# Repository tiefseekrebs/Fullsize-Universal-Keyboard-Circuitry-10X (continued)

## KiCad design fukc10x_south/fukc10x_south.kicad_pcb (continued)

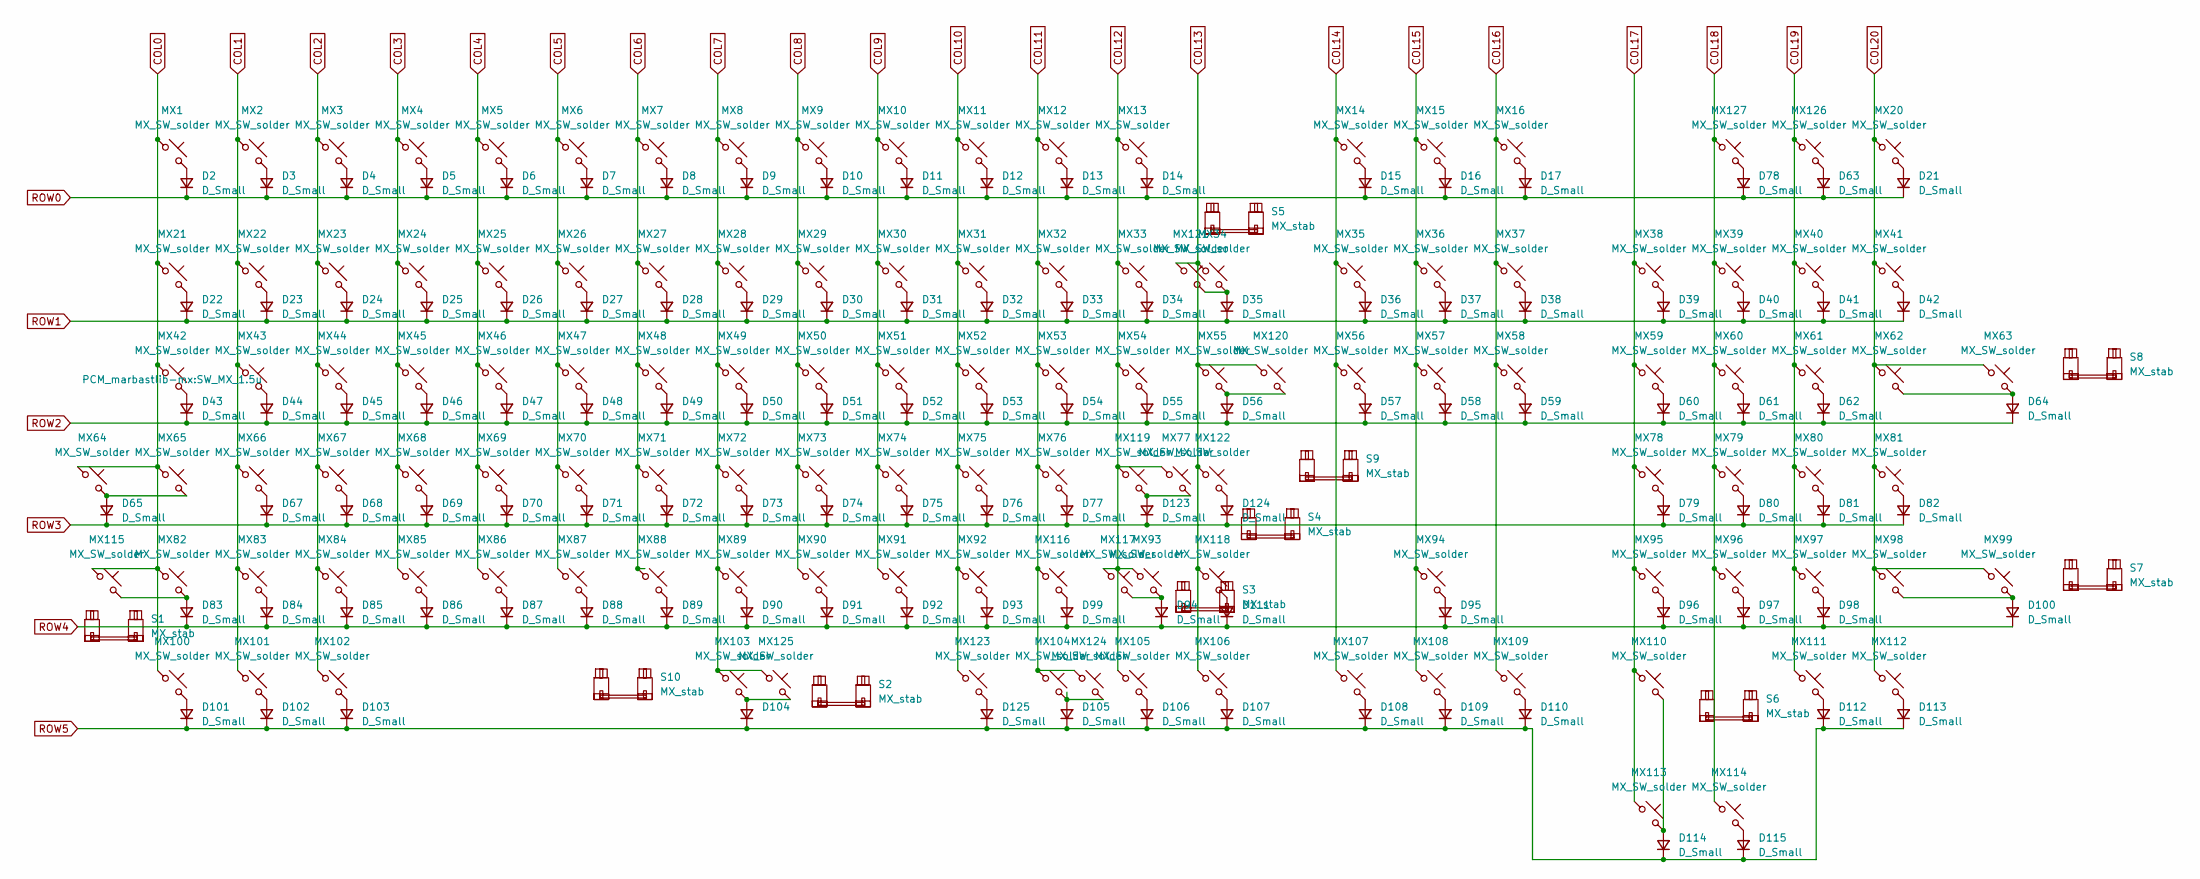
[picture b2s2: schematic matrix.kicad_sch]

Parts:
D2, D3, D4, D5, D6, D7, D8, D9, D10, D11, D12, D13, D14, D15, D16, D17, D21, D22, D23, D24, D25, D26, D27, D28, D29, D30, D31, D32, D33, D34, D35, D36, D37, D38, D39, D40, D41, D42, D43, D44, D45, D46, D47, D48, D49, D50, D51, D52, D53, D54, D55, D56, D57, D58, D59, D60, D61, D62, D63, D64, D65, D67, D68, D69, D70, D71, D72, D73, D74, D75, D76, D77, D78, D79, D80, D81, D82, D83, D84, D85, D86, D87, D88, D89, D90, D91, D92, D93, D94, D95, D96, D97, D98, D99, D100, D101, D102, D103, D104, D105, D106, D107, D108, D109, D110, D111, D112, D113, D114, D115, D123, D124, D125: D_Small; D_SOD-123; LCSC C81598
MX1, MX2, MX3, MX4, MX5, MX6, MX7, MX8, MX9, MX10, MX11, MX12, MX13, MX14, MX15, MX16, MX20, MX21, MX22, MX23, MX24, MX25, MX26, MX27, MX28, MX29, MX30, MX31, MX32, MX33, MX34, MX35, MX36, MX37, MX38, MX39, MX40, MX41, MX43, MX44, MX45, MX46, MX47, MX48, MX49, MX50, MX51, MX52, MX53, MX54, MX56, MX57, MX58, MX59, MX60, MX61, MX62, MX63, MX66, MX67, MX68, MX69, MX70, MX71, MX72, MX73, MX74, MX75, MX76, MX77, MX78, MX79, MX80, MX81, MX82, MX83, MX84, MX85, MX86, MX87, MX88, MX89, MX90, MX91, MX92, MX93, MX94, MX95, MX96, MX97, MX98, MX99, MX101, MX103, MX105, MX107, MX108, MX109, MX110, MX111, MX112, MX113, MX114, MX116, MX118, MX119, MX120, MX121, MX122, MX124, MX125, MX126, MX127: MX_SW_solder; SW_MX_1u
MX42, MX55, MX100, MX102, MX104, MX106, MX123: MX_SW_solder; SW_MX_1.5u
MX64, MX117: MX_SW_solder; SW_MX_1.75u
MX65: MX_SW_solder; SW_MX_1.75u_STP_1.25
MX115: MX_SW_solder; SW_MX_1.25u
S1, S4: MX_stab; STAB_MX_2.25u
S2: MX_stab; STAB_MX_7u
S3: MX_stab; STAB_MX_2.75u
S5, S6, S7, S8: MX_stab; STAB_MX_2u
S9: MX_stab; STAB_MX_ISO-ROT
S10: MX_stab; STAB_MX_6u

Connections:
COL0: MX1.1, MX21.1, MX42.1, MX64.1, MX65.1, MX82.1, MX100.1, MX115.1; also elsewhere on the board
COL1: MX2.1, MX22.1, MX43.1, MX66.1, MX83.1, MX101.1; also elsewhere on the board
COL2: MX3.1, MX23.1, MX44.1, MX67.1, MX84.1, MX102.1; also elsewhere on the board
COL3: MX4.1, MX24.1, MX45.1, MX68.1, MX85.1; also elsewhere on the board
COL4: MX5.1, MX25.1, MX46.1, MX69.1, MX86.1; also elsewhere on the board
COL5: MX6.1, MX26.1, MX47.1, MX70.1, MX87.1; also elsewhere on the board
COL6: MX7.1, MX27.1, MX48.1, MX71.1, MX88.1; also elsewhere on the board
COL7: MX8.1, MX28.1, MX49.1, MX72.1, MX89.1, MX103.1, MX125.1; also elsewhere on the board
COL8: MX9.1, MX29.1, MX50.1, MX73.1, MX90.1; also elsewhere on the board
COL9: MX10.1, MX30.1, MX51.1, MX74.1, MX91.1; also elsewhere on the board
COL10: MX11.1, MX31.1, MX52.1, MX75.1, MX92.1, MX123.1; also elsewhere on the board
COL11: MX12.1, MX32.1, MX53.1, MX76.1, MX104.1, MX116.1, MX124.1; also elsewhere on the board
COL12: MX13.1, MX33.1, MX54.1, MX77.1, MX93.1, MX105.1, MX117.1, MX119.1; also elsewhere on the board
COL13: MX34.1, MX55.1, MX106.1, MX118.1, MX120.1, MX121.1, MX122.1; also elsewhere on the board
COL14: MX14.1, MX35.1, MX56.1, MX107.1; also elsewhere on the board
COL15: MX15.1, MX36.1, MX57.1, MX94.1, MX108.1; also elsewhere on the board
COL16: MX16.1, MX37.1, MX58.1, MX109.1; also elsewhere on the board
COL17: MX38.1, MX59.1, MX78.1, MX95.1, MX110.1, MX113.1; also elsewhere on the board
COL18: MX39.1, MX60.1, MX79.1, MX96.1, MX114.1, MX127.1; also elsewhere on the board
COL19: MX40.1, MX61.1, MX80.1, MX97.1, MX111.1, MX126.1; also elsewhere on the board
COL20: MX20.1, MX41.1, MX62.1, MX63.1, MX81.1, MX98.1, MX99.1, MX112.1; also elsewhere on the board
unnamed: D2.2 (A), MX1.2
unnamed: D3.2 (A), MX2.2
unnamed: D4.2 (A), MX3.2
unnamed: D5.2 (A), MX4.2
unnamed: D6.2 (A), MX5.2
unnamed: D7.2 (A), MX6.2
unnamed: D8.2 (A), MX7.2
unnamed: D9.2 (A), MX8.2
unnamed: D10.2 (A), MX9.2
unnamed: D11.2 (A), MX10.2
unnamed: D12.2 (A), MX11.2
unnamed: D13.2 (A), MX12.2
unnamed: D14.2 (A), MX13.2
unnamed: D15.2 (A), MX14.2
unnamed: D16.2 (A), MX15.2
unnamed: D17.2 (A), MX16.2
unnamed: D21.2 (A), MX20.2
unnamed: D22.2 (A), MX21.2
unnamed: D23.2 (A), MX22.2
unnamed: D24.2 (A), MX23.2
unnamed: D25.2 (A), MX24.2
unnamed: D26.2 (A), MX25.2
unnamed: D27.2 (A), MX26.2
unnamed: D28.2 (A), MX27.2
unnamed: D29.2 (A), MX28.2
unnamed: D30.2 (A), MX29.2
unnamed: D31.2 (A), MX30.2
unnamed: D32.2 (A), MX31.2
unnamed: D33.2 (A), MX32.2
unnamed: D34.2 (A), MX33.2
unnamed: D35.2 (A), MX34.2, MX121.2
unnamed: D36.2 (A), MX35.2
unnamed: D37.2 (A), MX36.2
unnamed: D38.2 (A), MX37.2
unnamed: D39.2 (A), MX38.2
unnamed: D40.2 (A), MX39.2
unnamed: D41.2 (A), MX40.2
unnamed: D42.2 (A), MX41.2
unnamed: D43.2 (A), MX42.2
unnamed: D44.2 (A), MX43.2
unnamed: D45.2 (A), MX44.2
unnamed: D46.2 (A), MX45.2
unnamed: D47.2 (A), MX46.2
unnamed: D48.2 (A), MX47.2
unnamed: D49.2 (A), MX48.2
unnamed: D50.2 (A), MX49.2
unnamed: D51.2 (A), MX50.2
unnamed: D52.2 (A), MX51.2
unnamed: D53.2 (A), MX52.2
unnamed: D54.2 (A), MX53.2
unnamed: D55.2 (A), MX54.2
unnamed: D56.2 (A), MX55.2, MX120.2
unnamed: D57.2 (A), MX56.2
unnamed: D58.2 (A), MX57.2
unnamed: D59.2 (A), MX58.2
unnamed: D60.2 (A), MX59.2
unnamed: D61.2 (A), MX60.2
unnamed: D62.2 (A), MX61.2
unnamed: D63.2 (A), MX126.2
unnamed: D64.2 (A), MX62.2, MX63.2
unnamed: D65.2 (A), MX64.2, MX65.2
unnamed: D67.2 (A), MX66.2
unnamed: D68.2 (A), MX67.2
unnamed: D69.2 (A), MX68.2
unnamed: D70.2 (A), MX69.2
unnamed: D71.2 (A), MX70.2
unnamed: D72.2 (A), MX71.2
unnamed: D73.2 (A), MX72.2
unnamed: D74.2 (A), MX73.2
unnamed: D75.2 (A), MX74.2
unnamed: D76.2 (A), MX75.2
unnamed: D77.2 (A), MX76.2
unnamed: D78.2 (A), MX127.2
unnamed: D79.2 (A), MX78.2
unnamed: D80.2 (A), MX79.2
unnamed: D81.2 (A), MX80.2
unnamed: D82.2 (A), MX81.2
unnamed: D83.2 (A), MX82.2, MX115.2
unnamed: D84.2 (A), MX83.2
unnamed: D85.2 (A), MX84.2
unnamed: D86.2 (A), MX85.2
unnamed: D87.2 (A), MX86.2
unnamed: D88.2 (A), MX87.2
unnamed: D89.2 (A), MX88.2
unnamed: D90.2 (A), MX89.2
unnamed: D91.2 (A), MX90.2
unnamed: D92.2 (A), MX91.2
unnamed: D93.2 (A), MX92.2
unnamed: D94.2 (A), MX93.2, MX117.2
unnamed: D95.2 (A), MX94.2
unnamed: D96.2 (A), MX95.2
unnamed: D97.2 (A), MX96.2
unnamed: D98.2 (A), MX97.2
unnamed: D99.2 (A), MX116.2
unnamed: D100.2 (A), MX98.2, MX99.2
unnamed: D101.2 (A), MX100.2
unnamed: D102.2 (A), MX101.2
unnamed: D103.2 (A), MX102.2
unnamed: D104.2 (A), MX103.2, MX125.2
unnamed: D105.2 (A), MX104.2, MX124.2
unnamed: D106.2 (A), MX105.2
unnamed: D107.2 (A), MX106.2
unnamed: D108.2 (A), MX107.2
unnamed: D109.2 (A), MX108.2
unnamed: D110.2 (A), MX109.2
unnamed: D111.2 (A), MX118.2
unnamed: D112.2 (A), MX111.2
unnamed: D113.2 (A), MX112.2
unnamed: D114.2 (A), MX110.2, MX113.2
unnamed: D115.2 (A), MX114.2
unnamed: D123.2 (A), MX77.2, MX119.2
unnamed: D124.2 (A), MX122.2
unnamed: D125.2 (A), MX123.2
ROW0: D2.1 (K), D3.1 (K), D4.1 (K), D5.1 (K), D6.1 (K), D7.1 (K), D8.1 (K), D9.1 (K), D10.1 (K), D11.1 (K), D12.1 (K), D13.1 (K), D14.1 (K), D15.1 (K), D16.1 (K), D17.1 (K), D21.1 (K), D63.1 (K), D78.1 (K); also elsewhere on the board
ROW1: D22.1 (K), D23.1 (K), D24.1 (K), D25.1 (K), D26.1 (K), D27.1 (K), D28.1 (K), D29.1 (K), D30.1 (K), D31.1 (K), D32.1 (K), D33.1 (K), D34.1 (K), D35.1 (K), D36.1 (K), D37.1 (K), D38.1 (K), D39.1 (K), D40.1 (K), D41.1 (K), D42.1 (K); also elsewhere on the board
ROW2: D43.1 (K), D44.1 (K), D45.1 (K), D46.1 (K), D47.1 (K), D48.1 (K), D49.1 (K), D50.1 (K), D51.1 (K), D52.1 (K), D53.1 (K), D54.1 (K), D55.1 (K), D56.1 (K), D57.1 (K), D58.1 (K), D59.1 (K), D60.1 (K), D61.1 (K), D62.1 (K), D64.1 (K); also elsewhere on the board
ROW3: D65.1 (K), D67.1 (K), D68.1 (K), D69.1 (K), D70.1 (K), D71.1 (K), D72.1 (K), D73.1 (K), D74.1 (K), D75.1 (K), D76.1 (K), D77.1 (K), D79.1 (K), D80.1 (K), D81.1 (K), D82.1 (K), D123.1 (K), D124.1 (K); also elsewhere on the board
ROW4: D83.1 (K), D84.1 (K), D85.1 (K), D86.1 (K), D87.1 (K), D88.1 (K), D89.1 (K), D90.1 (K), D91.1 (K), D92.1 (K), D93.1 (K), D94.1 (K), D95.1 (K), D96.1 (K), D97.1 (K), D98.1 (K), D99.1 (K), D100.1 (K), D111.1 (K); also elsewhere on the board
ROW5: D101.1 (K), D102.1 (K), D103.1 (K), D104.1 (K), D105.1 (K), D106.1 (K), D107.1 (K), D108.1 (K), D109.1 (K), D110.1 (K), D112.1 (K), D113.1 (K), D114.1 (K), D115.1 (K), D125.1 (K); also elsewhere on the board

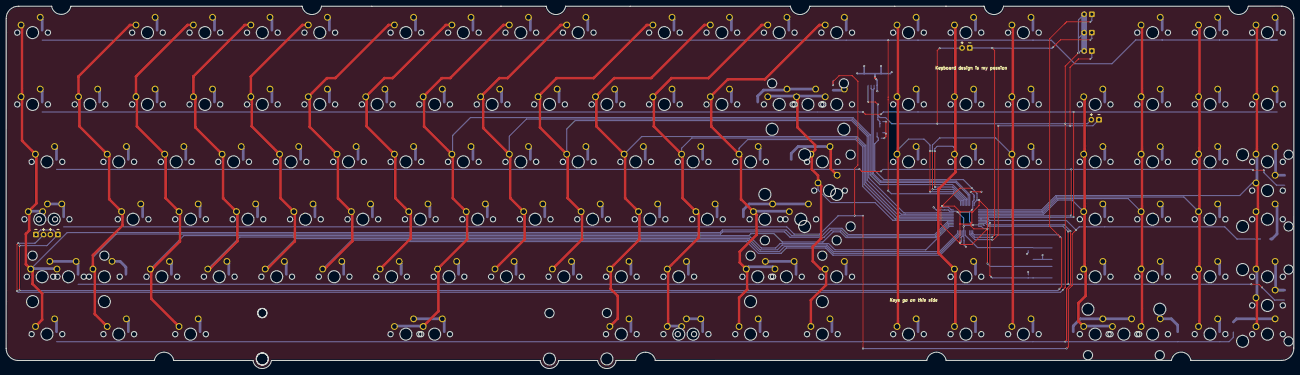
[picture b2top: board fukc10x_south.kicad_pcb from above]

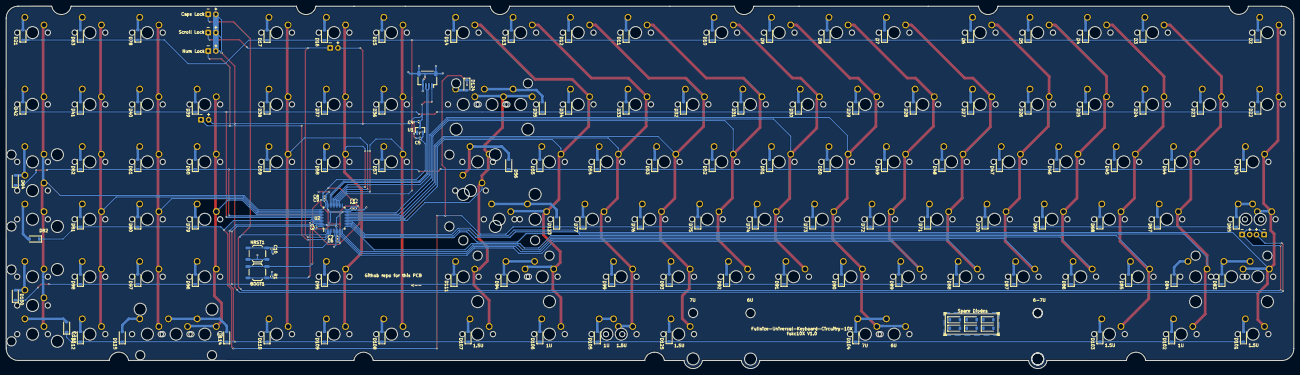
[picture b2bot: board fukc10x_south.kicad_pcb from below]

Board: 2 copper layers, 427.1 x 120.2 mm, 276 parts (135 on the bottom side), 150 nets.

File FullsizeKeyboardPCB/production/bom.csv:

Designator,Footprint,Quantity,Value,LCSC Part #
BOOT1,SW_SPST_TL3342,1,SW_BOOT0,
"C1, C8",0402,2,4.7uF,C23733
C10,0402,1,100nF,
"C2, C3, C7, C9",0402,4,100nF,C1525
"C4, C5, C6",0402,3,1uF,C52923
D1,SOT-143,1,PRTR5V0U2X,C2827688
"D10, D100, D101, D102, D103, D104, D105, D106, D107, D108, D109, D11, D110, D112, D113, D114, D115, D12, D13, D14, D15, D16, D17, D18, D19, D2, D20, D21, D22, D23, D24, D25, D26, D27, D28, D29, D3, D30, D31, D32, D33, D34, D35, D36, D37, D38, D39, D4, D40, D41, D42, D43, D44, D45, D46, D47, D48, D49, D5, D50, D51, D52, D53, D54, D55, D56, D57, D58, D59, D6, D60, D61, D62, D64, D65, D67, D68, D69, D7, D70, D71, D72, D73, D74, D75, D76, D77, D78, D79, D8, D80, D81, D82, D83, D84, D85, D86, D87, D88, D89, D9, D90, D91, D92, D93, D94, D95, D96, D97, D98",D_SOD-123,110,D_Small,
F1,1206,1,500mA,
J1,JST_SH_SM04B-SRSS-TB_1x04-1MP_P1.00mm_Horizontal,1,SM04B-SRSS-TB,C160404
"MX1, MX10, MX101, MX103, MX105, MX107, MX108, MX109, MX11, MX110, MX111, MX112, MX113, MX114, MX12, MX13, MX14, MX15, MX16, MX17, MX18, MX19, MX2, MX20, MX21, MX22, MX23, MX24, MX25, MX26, MX27, MX28, MX29, MX3, MX30, MX31, MX32, MX33, MX34, MX35, MX36, MX37, MX38, MX39, MX4, MX40, MX41, MX43, MX44, MX45, MX46, MX47, MX48, MX49, MX5, MX50, MX51, MX52, MX53, MX54, MX56, MX57, MX58, MX59, MX6, MX60, MX61, MX62, MX63, MX66, MX67, MX68, MX69, MX7, MX70, MX71, MX72, MX73, MX74, MX75, MX76, MX77, MX78, MX79, MX8, MX80, MX81, MX82, MX83, MX84, MX85, MX86, MX87, MX88, MX89, MX9, MX90, MX91, MX92, MX93, MX94, MX95, MX96, MX97, MX98, MX99",SW_MX_1u,106,MX_SW_solder,
"MX100, MX102, MX104, MX106, MX42, MX55",SW_MX_1.5u,6,MX_SW_solder,
MX64,SW_MX_1.75u,1,MX_SW_solder,
MX65,SW_MX_1.75u_STP_1.25,1,MX_SW_solder,
NRST1,SW_SPST_TL3342,1,SW_NRST,
R1,0402,1,10k,
"S1, S4",STAB_MX_2.25u,2,MX_stab,
S2,STAB_MX_7u,1,MX_stab,
S3,STAB_MX_2.75u,1,MX_stab,
"S5, S6, S7, S8",STAB_MX_2u,4,MX_stab,
U1,SOT-23,1,XC6206P332MR,C5446
U2,LQFP-48_7x7mm_P0.5mm,1,STM32F072CBT6,C81720

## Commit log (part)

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2026-06-07 Add PCB files
2026-06-07 Add PCB files again
2026-06-07 refactor/remove old files
2026-06-07 further cleanup
2026-06-08 Extended Matrix. Added split r-shift and split l-shift. LED support. Removed three of the 4 top right keys because ugly and to make space for indicator leds there
2026-06-08 Added some Silkscreen Text aswell as spare diodes
2026-06-09 Diodes moved, ISO enter added, Som Silkscreens moved aswell. Generally some cleanup
2026-06-11 added split backspace + some updates to the matrix
2026-06-13 silkscreen adjustment. 87U bottom row with 6u spacebar added.
2026-06-15 adjusted spare diodes and some rounting. Updated step and production files
2026-06-15 wow readme
2026-06-15 Update README.md again
2026-06-17 updated LED Symbols + removed unnessecarry components for ESD and fusing
2026-06-18 added back keys above numpad + updated step file/prod stuff
2026-06-20 Soutfacing spacebar + zero Diode moved
2026-06-20 Update README.md
    ups
2026-06-20 typo in readme
2026-06-20 render, neue step dateien
2026-06-23 south and north variant
2026-06-23 update directorys
2026-06-23 update prod data
2026-06-23 moved forgotten leds
2026-06-23 ignore .history folders
2026-06-23 cleanup dutys
2026-06-23 update render
